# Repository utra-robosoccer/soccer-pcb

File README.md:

TODO's
  - SPI com between mcus
  - validate pinout with firmware
  -

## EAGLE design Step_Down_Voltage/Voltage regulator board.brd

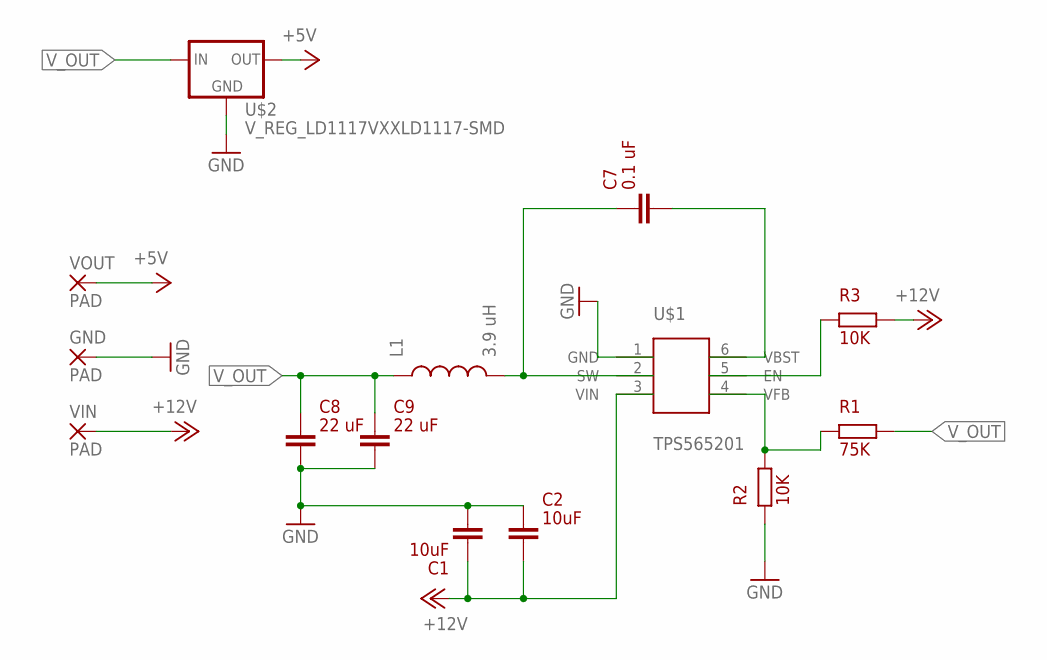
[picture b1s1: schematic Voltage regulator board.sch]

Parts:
C1, C2: 10uF; C1206K
C7: 0.1 uF; C1206K
C8, C9: 22 uF; C1206K
GND: PAD
L1: 3.9 uH; SRN6028
R1: 75K; C0603K
R2, R3: 10K; C0603K
U$1: TPS565201; SOT23-6
U$2: V_REG_LD1117VXXLD1117-SMD; SOT223
VIN: PAD
VOUT: PAD

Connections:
+5V: U$2.2 (OUT), VOUT.1
+12V: C1.1, C2.2, R3.2, U$1.3 (VIN), VIN.1
GND: C1.2, C2.1, C8.2, C9.2, GND.1, R2.1, U$1.1 (GND), U$2.1 (GND)
unnamed: C7.1, L1.P$2 (2), U$1.2 (SW)
unnamed: R1.1, R2.2, U$1.4 (VFB)
unnamed: R3.1, U$1.5 (EN)
unnamed: C7.2, U$1.6 (VBST)
V_OUT: C8.1, C9.1, L1.P$1 (1), R1.2, U$2.3 (IN)

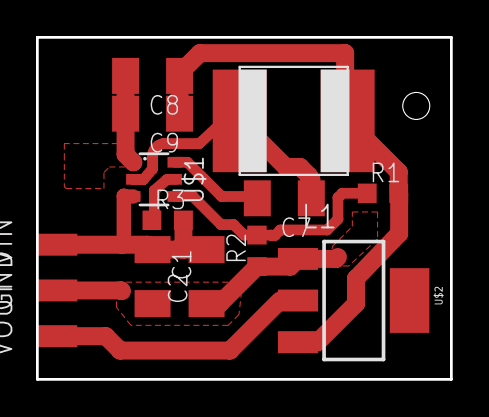
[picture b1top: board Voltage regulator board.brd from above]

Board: 2 copper layers, 23.0 x 19.0 mm, 14 parts (0 on the bottom side), 8 nets.

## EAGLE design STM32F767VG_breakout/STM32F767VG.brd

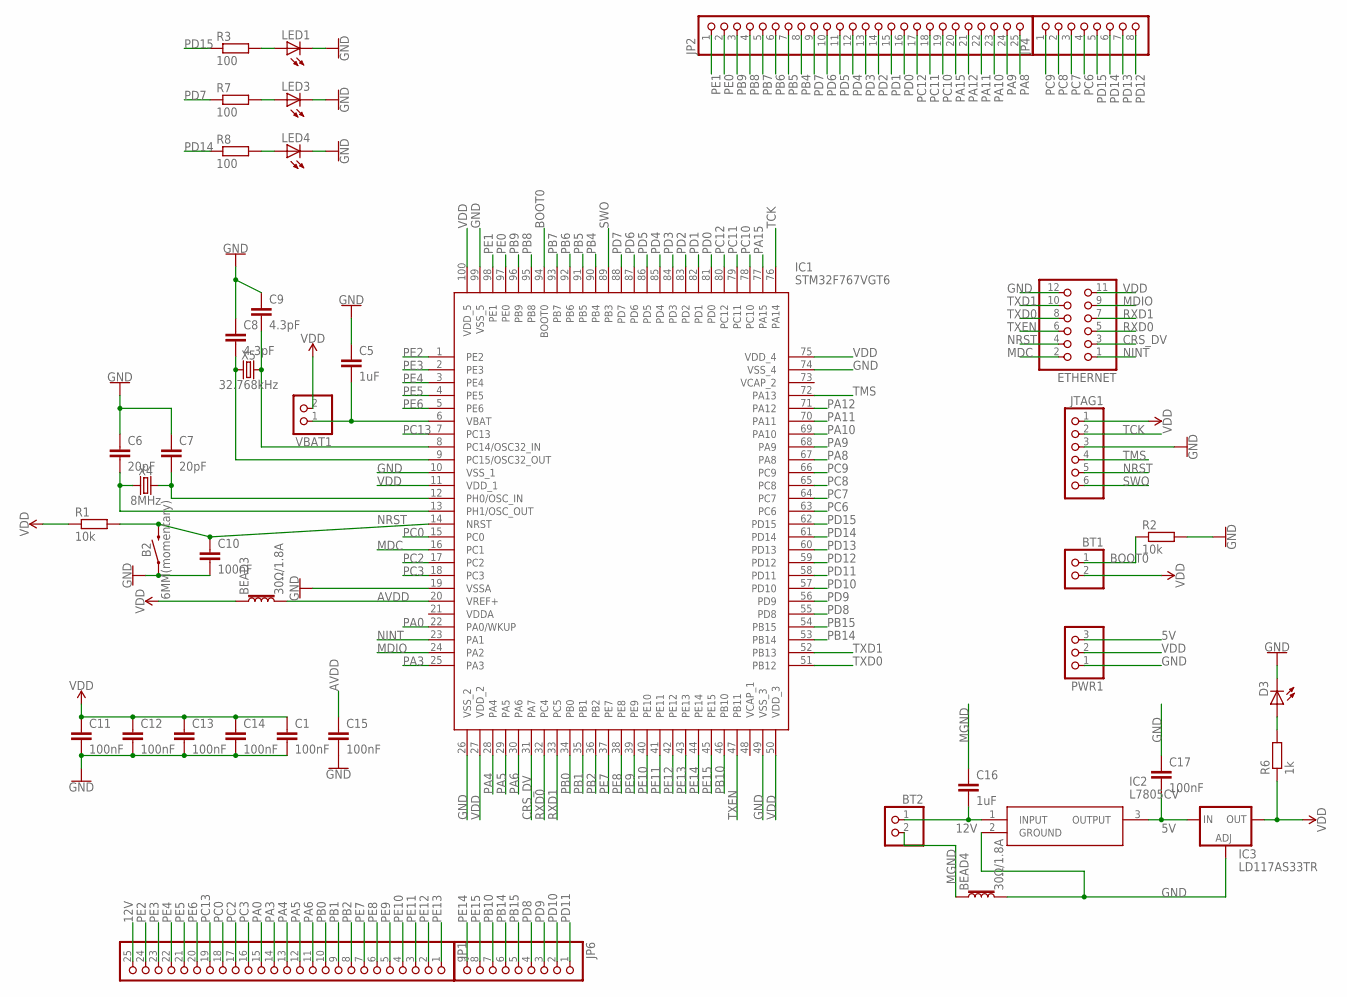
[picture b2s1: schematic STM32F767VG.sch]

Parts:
B2: 6MM(momentary); TACTILE_SWITCH_PTH_6.0MM
BEAD3, BEAD4: 30Ω/1.8A; 0603
BT1, BT2: PINHD-1X2; 1X02
C1, C10, C11, C12, C13, C14, C15, C17: 100nF; C0805
C5, C16: 1uF; C0805
C6, C7: 20pF; C0805
C8, C9: 4.3pF; C0805
D3: LED_E; LED_1206
ETHERNET: PINHD-2X6; 2X06
IC1: STM32F767VGT6; QFP50P1600X1600X160-100N
IC2: L7805CV; TO270P460X1020X2008-3P
IC3: LD117AS33TR; SOT223
JP1, JP2: PINHD-1X25; 1X25
JP4: PINHD-1X8; 1X08
JP6: PINHD-1X9; 1X09
JTAG1: PINHD-1X6; 1X06
LED1, LED3, LED4: LED_E; LED_1206
PWR1: PINHD-1X3; 1X03
R1, R2: 10k; R0805
R3, R7, R8: 100; R0805
R6: 1k; R0805
VBAT1: PINHD-1X2; 1X02
X4: 8MHz; HC49UP
X5: 32.768kHz; CRYSTAL-PTH-2X6-CYL

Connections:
5V: C17.2, IC2.3 (OUTPUT), IC3.3 (IN), PWR1.3
12V: BT2.1, C16.2, IC2.1 (INPUT), JP1.25
AVDD: BEAD3.2, C15.1, IC1.20 (VREF+)
BOOT0: BT1.1, IC1.94 (BOOT0), R2.1
CRS_DV: ETHERNET.3, IC1.31 (PA7)
GND: B2.1, BEAD4.2, C1.2, C5.1, C6.1, C7.1, C8.1, C9.1, C10.2, C11.2, C12.2, C13.2, C14.2, C15.2, C17.1, D3.C, ETHERNET.12, IC1.10 (VSS_1), IC1.19 (VSSA), IC1.26 (VSS_2), IC1.49 (VSS_3), IC1.74 (VSS_4), IC1.99 (VSS_5), IC2.2 (GROUND), IC3.1 (ADJ), JTAG1.3, LED1.C, LED3.C, LED4.C, PWR1.1, R2.2
MDC: ETHERNET.2, IC1.16 (PC1)
MDIO: ETHERNET.9, IC1.24 (PA2)
MGND: BEAD4.1, BT2.2, C16.1
unnamed: C5.2, IC1.6 (VBAT), VBAT1.1
unnamed: C9.2, IC1.8 (PC14/OSC32_IN), X5.2
unnamed: C8.2, IC1.9 (PC15/OSC32_OUT), X5.1
unnamed: LED1.A, R3.2
unnamed: C6.2, IC1.13 (PH1/OSC_OUT), X4.1
unnamed: C7.2, IC1.12 (PH0/OSC_IN), X4.2
unnamed: D3.A, R6.2
unnamed: LED3.A, R7.2
unnamed: LED4.A, R8.2
NINT: ETHERNET.1, IC1.23 (PA1)
NRST: B2.3 (2), C10.1, ETHERNET.4, IC1.14 (NRST), JTAG1.5, R1.2
PA0: IC1.22 (PA0/WKUP), JP1.15
PA3: IC1.25 (PA3), JP1.14
PA4: IC1.28 (PA4), JP1.13
PA5: IC1.29 (PA5), JP1.12
PA6: IC1.30 (PA6), JP1.11
PA8: IC1.67 (PA8), JP2.25
PA9: IC1.68 (PA9), JP2.24
PA10: IC1.69 (PA10), JP2.23
PA11: IC1.70 (PA11), JP2.22
PA12: IC1.71 (PA12), JP2.21
PA15: IC1.77 (PA15), JP2.20
PB0: IC1.34 (PB0), JP1.10
PB1: IC1.35 (PB1), JP1.9
PB2: IC1.36 (PB2), JP1.8
PB4: IC1.90 (PB4), JP2.8
PB5: IC1.91 (PB5), JP2.7
PB6: IC1.92 (PB6), JP2.6
PB7: IC1.93 (PB7), JP2.5
PB8: IC1.95 (PB8), JP2.4
PB9: IC1.96 (PB9), JP2.3
PB10: IC1.46 (PB10), JP6.7
PB14: IC1.53 (PB14), JP6.6
PB15: IC1.54 (PB15), JP6.5
PC0: IC1.15 (PC0), JP1.18
PC2: IC1.17 (PC2), JP1.17
PC3: IC1.18 (PC3), JP1.16
PC6: IC1.63 (PC6), JP4.4
PC7: IC1.64 (PC7), JP4.3
PC8: IC1.65 (PC8), JP4.2
PC9: IC1.66 (PC9), JP4.1
PC10: IC1.78 (PC10), JP2.19
PC11: IC1.79 (PC11), JP2.18
PC12: IC1.80 (PC12), JP2.17
PC13: IC1.7 (PC13), JP1.19
PD0: IC1.81 (PD0), JP2.16
PD1: IC1.82 (PD1), JP2.15
PD2: IC1.83 (PD2), JP2.14
PD3: IC1.84 (PD3), JP2.13
PD4: IC1.85 (PD4), JP2.12
PD5: IC1.86 (PD5), JP2.11
PD6: IC1.87 (PD6), JP2.10
PD7: IC1.88 (PD7), JP2.9, R7.1
PD8: IC1.55 (PD8), JP6.4
PD9: IC1.56 (PD9), JP6.3
PD10: IC1.57 (PD10), JP6.2
PD11: IC1.58 (PD11), JP6.1
PD12: IC1.59 (PD12), JP4.8
PD13: IC1.60 (PD13), JP4.7
PD14: IC1.61 (PD14), JP4.6, R8.1
PD15: IC1.62 (PD15), JP4.5, R3.1
PE0: IC1.97 (PE0), JP2.2
PE1: IC1.98 (PE1), JP2.1
PE2: IC1.1 (PE2), JP1.24
PE3: IC1.2 (PE3), JP1.23
PE4: IC1.3 (PE4), JP1.22
PE5: IC1.4 (PE5), JP1.21
PE6: IC1.5 (PE6), JP1.20
PE7: IC1.37 (PE7), JP1.7
PE8: IC1.38 (PE8), JP1.6
PE9: IC1.39 (PE9), JP1.5
PE10: IC1.40 (PE10), JP1.4
PE11: IC1.41 (PE11), JP1.3
PE12: IC1.42 (PE12), JP1.2
PE13: IC1.43 (PE13), JP1.1
PE14: IC1.44 (PE14), JP6.9
PE15: IC1.45 (PE15), JP6.8
RXD0: ETHERNET.5, IC1.32 (PC4)
RXD1: ETHERNET.7, IC1.33 (PC5)
SWO: IC1.89 (PB3), JTAG1.6
TCK: IC1.76 (PA14), JTAG1.2
TMS: IC1.72 (PA13), JTAG1.4
TXD0: ETHERNET.8, IC1.51 (PB12)
TXD1: ETHERNET.10, IC1.52 (PB13)
TXEN: ETHERNET.6, IC1.47 (PB11)
VCAP_1: IC1.48 (VCAP_1)
VCAP_2: IC1.73 (VCAP_2)
VDD: BEAD3.1, BT1.2, C1.1, C11.1, C12.1, C13.1, C14.1, ETHERNET.11, IC1.11 (VDD_1), IC1.27 (VDD_2), IC1.50 (VDD_3), IC1.75 (VDD_4), IC1.100 (VDD_5), IC3.4 (OUT), JTAG1.1, PWR1.2, R1.1, R6.1, VBAT1.2
VDDA: IC1.21 (VDDA)

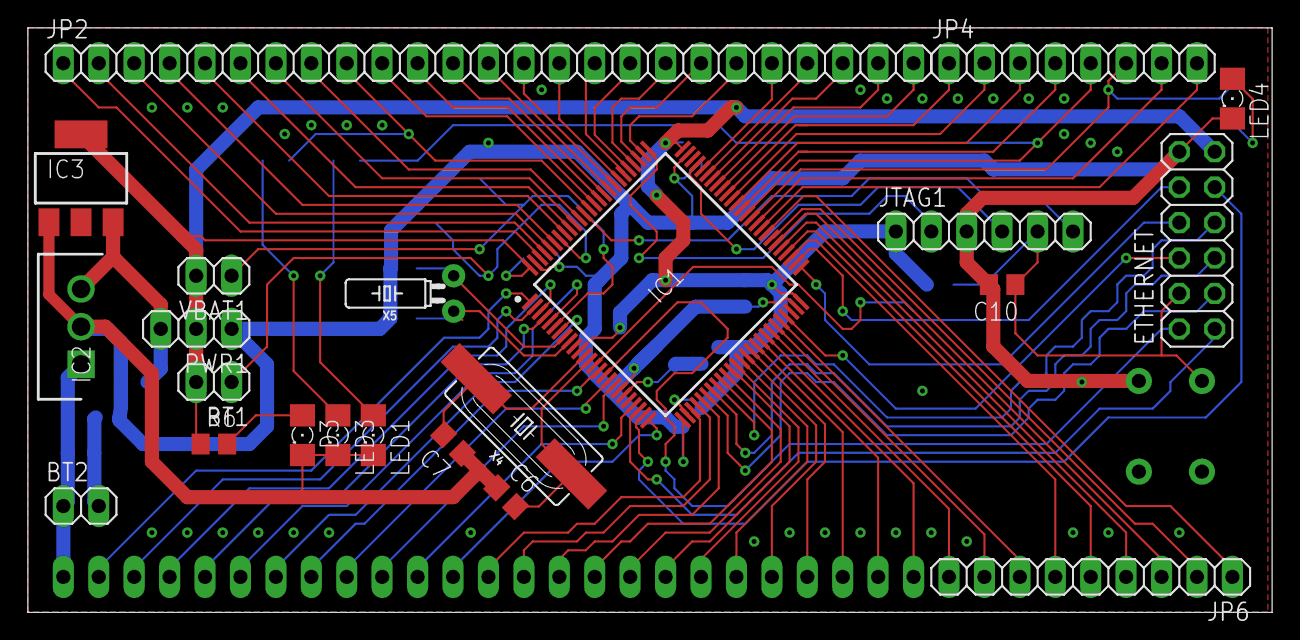
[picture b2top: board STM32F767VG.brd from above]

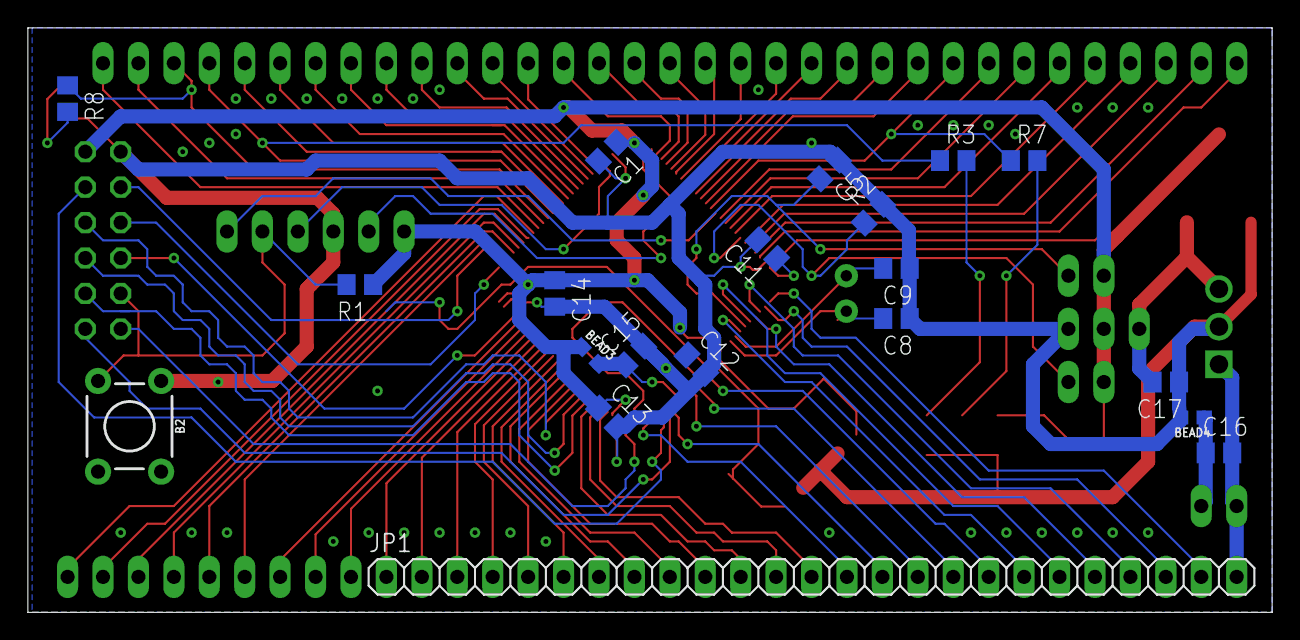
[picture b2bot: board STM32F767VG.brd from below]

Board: 2 copper layers, 89.2 x 41.9 mm, 42 parts (20 on the bottom side), 95 nets.

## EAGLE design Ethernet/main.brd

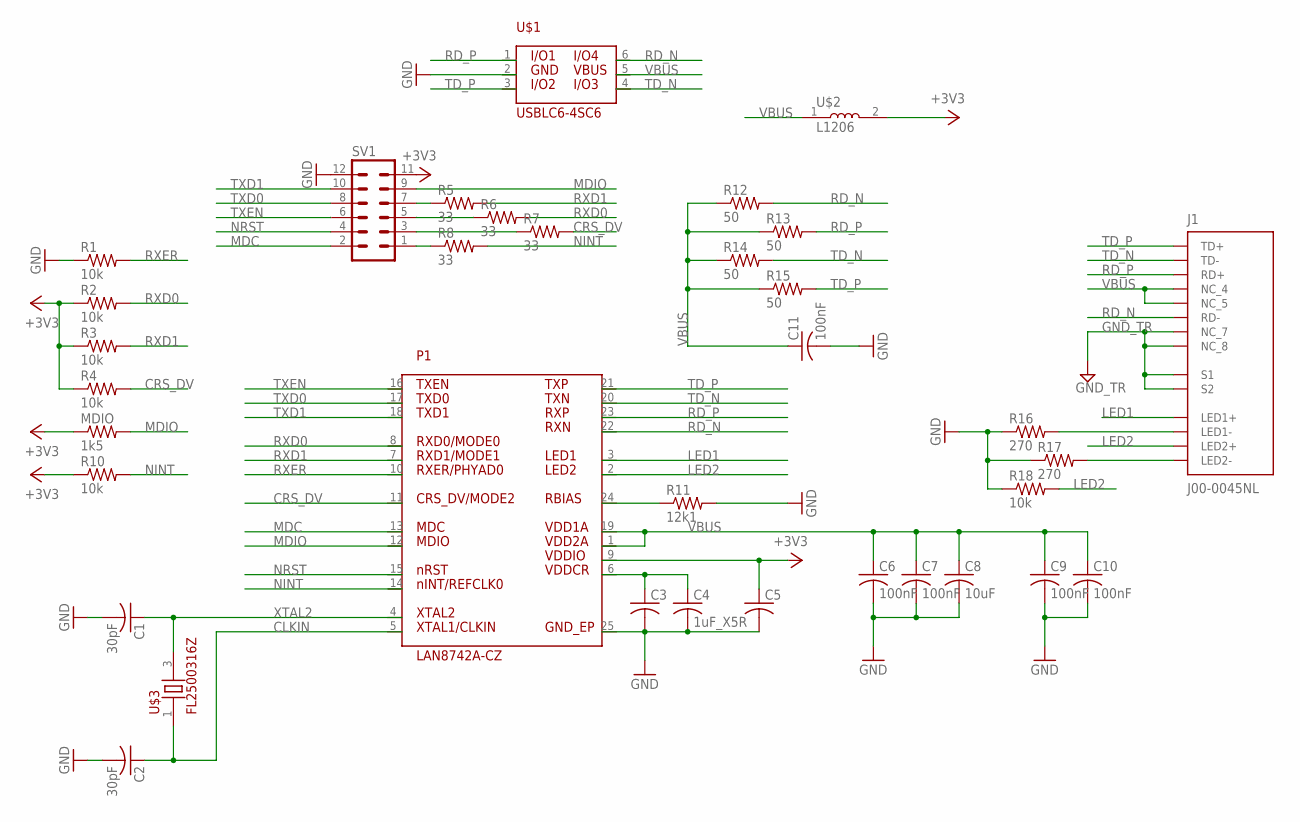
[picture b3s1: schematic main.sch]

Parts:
C1, C2: 30pF; C0603
C3, C5: C-USC0603; C0603
C4: 1uF_X5R; C0603
C6, C7, C9, C10, C11: 100nF; C0603
C8: 10uF; C1206K
J1: J00-0045NL; PULSE_J00-0045NL
MDIO: 1k5; R0603
P1: LAN8742A-CZ
R1, R2, R3, R4, R10, R18: 10k; R0603
R5, R6, R7, R8: 33; R0603
R11: 12k1; R0603
R12, R13, R14, R15: 50; R0603
R16, R17: 270; R0603
SV1: MA06-2
U$1: USBLC6-4SC6; SOT95P280X145-6N
U$2: L1206; RESC3216X125N
U$3: FL2500316Z

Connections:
+3V3: C5.1, MDIO.1, P1.9, R2.1, R3.1, R4.1, R10.1, SV1.11, U$2.2
CLKIN: C2.1, P1.5, U$3.1
CRS_DV: P1.11, R4.2, R7.2
GND: C1.2, C2.2, C3.2, C4.2, C5.2, C6.2, C7.2, C8.2, C9.2, C10.2, C11.2, P1.25, R1.1, R11.2, R16.1, R17.1, R18.1, SV1.12, U$1.2
GND_TR: J1.7 (NC_7), J1.8 (NC_8), J1.S1, J1.S2
LED1: J1.9 (LED1+), P1.3
LED2: J1.12 (LED2+), P1.2, R18.2
MDC: P1.13, SV1.2
MDIO: MDIO.2, P1.12, SV1.9
unnamed: R5.1, SV1.7
unnamed: R6.1, SV1.5
unnamed: P1.24, R11.1
unnamed: R7.1, SV1.3
unnamed: R8.1, SV1.1
unnamed: C3.1, C4.1, P1.6
unnamed: J1.10 (LED1-), R16.2
unnamed: J1.11 (LED2-), R17.2
NINT: P1.14, R8.2, R10.2
NRST: P1.15, SV1.4
RD_N: J1.6 (RD-), P1.22, R12.2, U$1.6
RD_P: J1.3 (RD+), P1.23, R13.2, U$1.1
RXD0: P1.8, R2.2, R6.2
RXD1: P1.7, R3.2, R5.2
RXER: P1.10, R1.2
TD_N: J1.2 (TD-), P1.20, R14.2, U$1.4
TD_P: J1.1 (TD+), P1.21, R15.2, U$1.3
TXD0: P1.17, SV1.8
TXD1: P1.18, SV1.10
TXEN: P1.16, SV1.6
VBUS: C6.1, C7.1, C8.1, C9.1, C10.1, C11.1, J1.4 (NC_4), J1.5 (NC_5), P1.1, P1.19, R12.1, R13.1, R14.1, R15.1, U$1.5, U$2.1
XTAL2: C1.1, P1.4, U$3.3

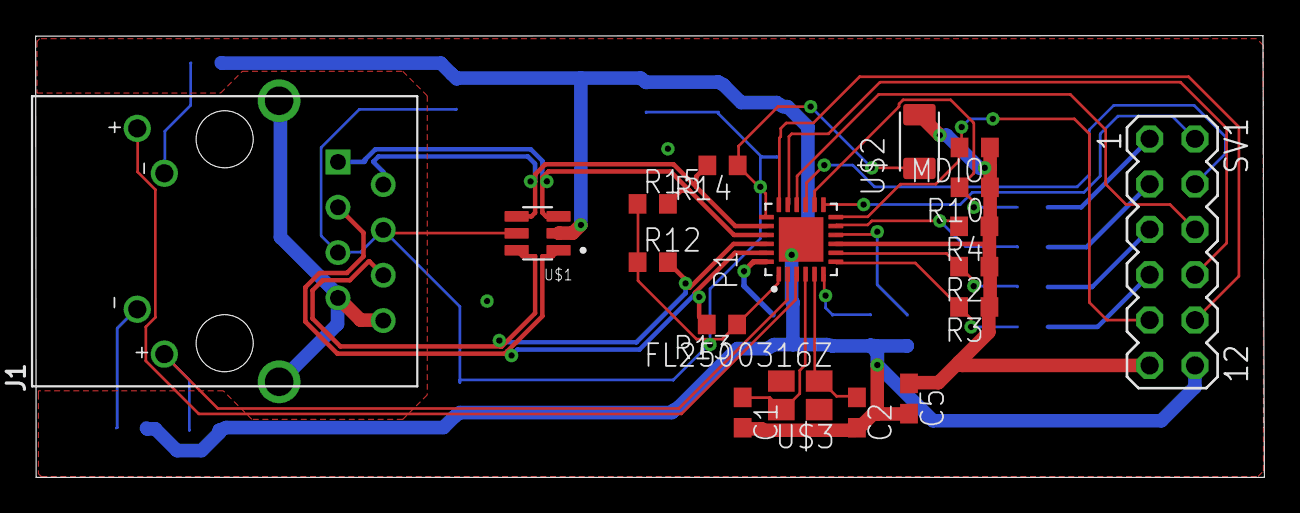
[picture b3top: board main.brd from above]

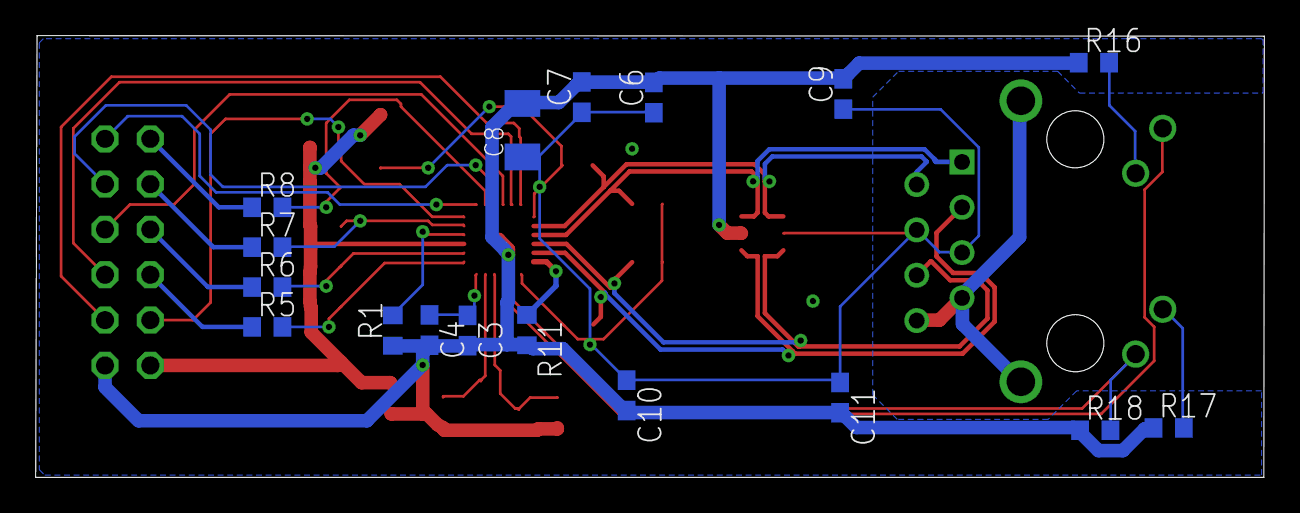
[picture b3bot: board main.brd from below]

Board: 2 copper layers, 68.9 x 24.8 mm, 35 parts (17 on the bottom side), 31 nets.

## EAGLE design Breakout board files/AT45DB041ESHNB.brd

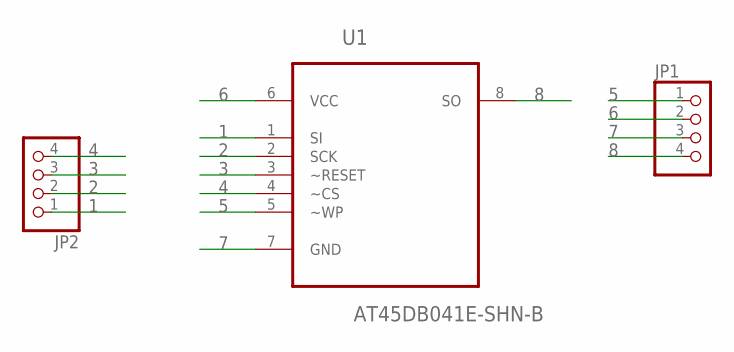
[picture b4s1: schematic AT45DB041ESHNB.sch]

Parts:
JP1, JP2: PINHD-1X4; 1X04
U1: AT45DB041E-SHN-B; SOIC127P798X216-8N

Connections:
1: JP2.1, U1.1 (SI)
2: JP2.2, U1.2 (SCK)
3: JP2.3, U1.3 (~RESET)
4: JP2.4, U1.4 (~CS)
5: JP1.1, U1.5 (~WP)
6: JP1.2, U1.6 (VCC)
7: JP1.3, U1.7 (GND)
8: JP1.4, U1.8 (SO)

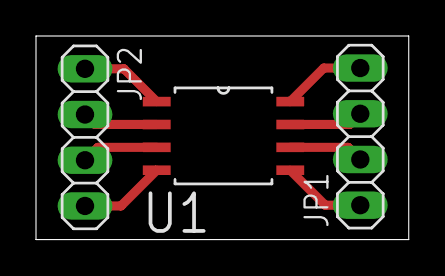
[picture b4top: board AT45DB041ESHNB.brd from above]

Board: 2 copper layers, 20.7 x 11.3 mm, 3 parts (0 on the bottom side), 8 nets.

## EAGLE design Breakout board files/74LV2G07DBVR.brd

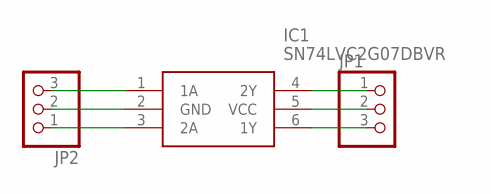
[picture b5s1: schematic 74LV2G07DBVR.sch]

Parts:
IC1: SN74LVC2G07DBVR; SOT95P280X145-6N
JP1, JP2: PINHD-1X3; 1X03

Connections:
unnamed: IC1.2 (GND), JP2.2
unnamed: IC1.1 (1A), JP2.3
unnamed: IC1.3 (2A), JP2.1
unnamed: IC1.6 (1Y), JP1.3
unnamed: IC1.4 (2Y), JP1.1
unnamed: IC1.5 (VCC), JP1.2

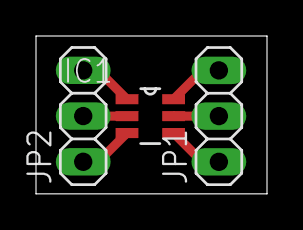
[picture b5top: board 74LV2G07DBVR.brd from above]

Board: 2 copper layers, 12.8 x 8.8 mm, 3 parts (0 on the bottom side), 6 nets.

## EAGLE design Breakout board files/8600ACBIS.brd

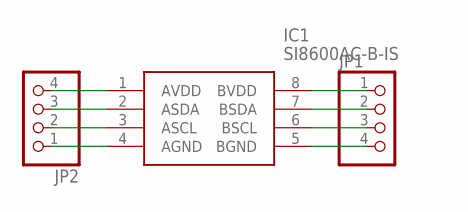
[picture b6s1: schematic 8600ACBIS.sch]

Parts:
IC1: SI8600AC-B-IS; SOIC127P600X175-8N
JP1, JP2: PINHD-1X4; 1X04

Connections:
unnamed: IC1.1 (AVDD), JP2.4
unnamed: IC1.2 (ASDA), JP2.3
unnamed: IC1.3 (ASCL), JP2.2
unnamed: IC1.4 (AGND), JP2.1
unnamed: IC1.8 (BVDD), JP1.1
unnamed: IC1.7 (BSDA), JP1.2
unnamed: IC1.6 (BSCL), JP1.3
unnamed: IC1.5 (BGND), JP1.4

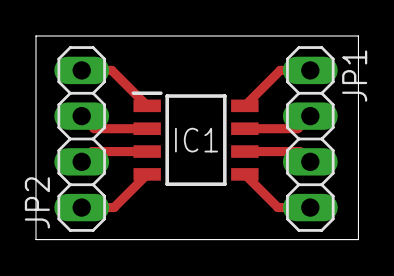
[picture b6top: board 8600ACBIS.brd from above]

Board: 2 copper layers, 17.9 x 11.3 mm, 3 parts (0 on the bottom side), 8 nets.

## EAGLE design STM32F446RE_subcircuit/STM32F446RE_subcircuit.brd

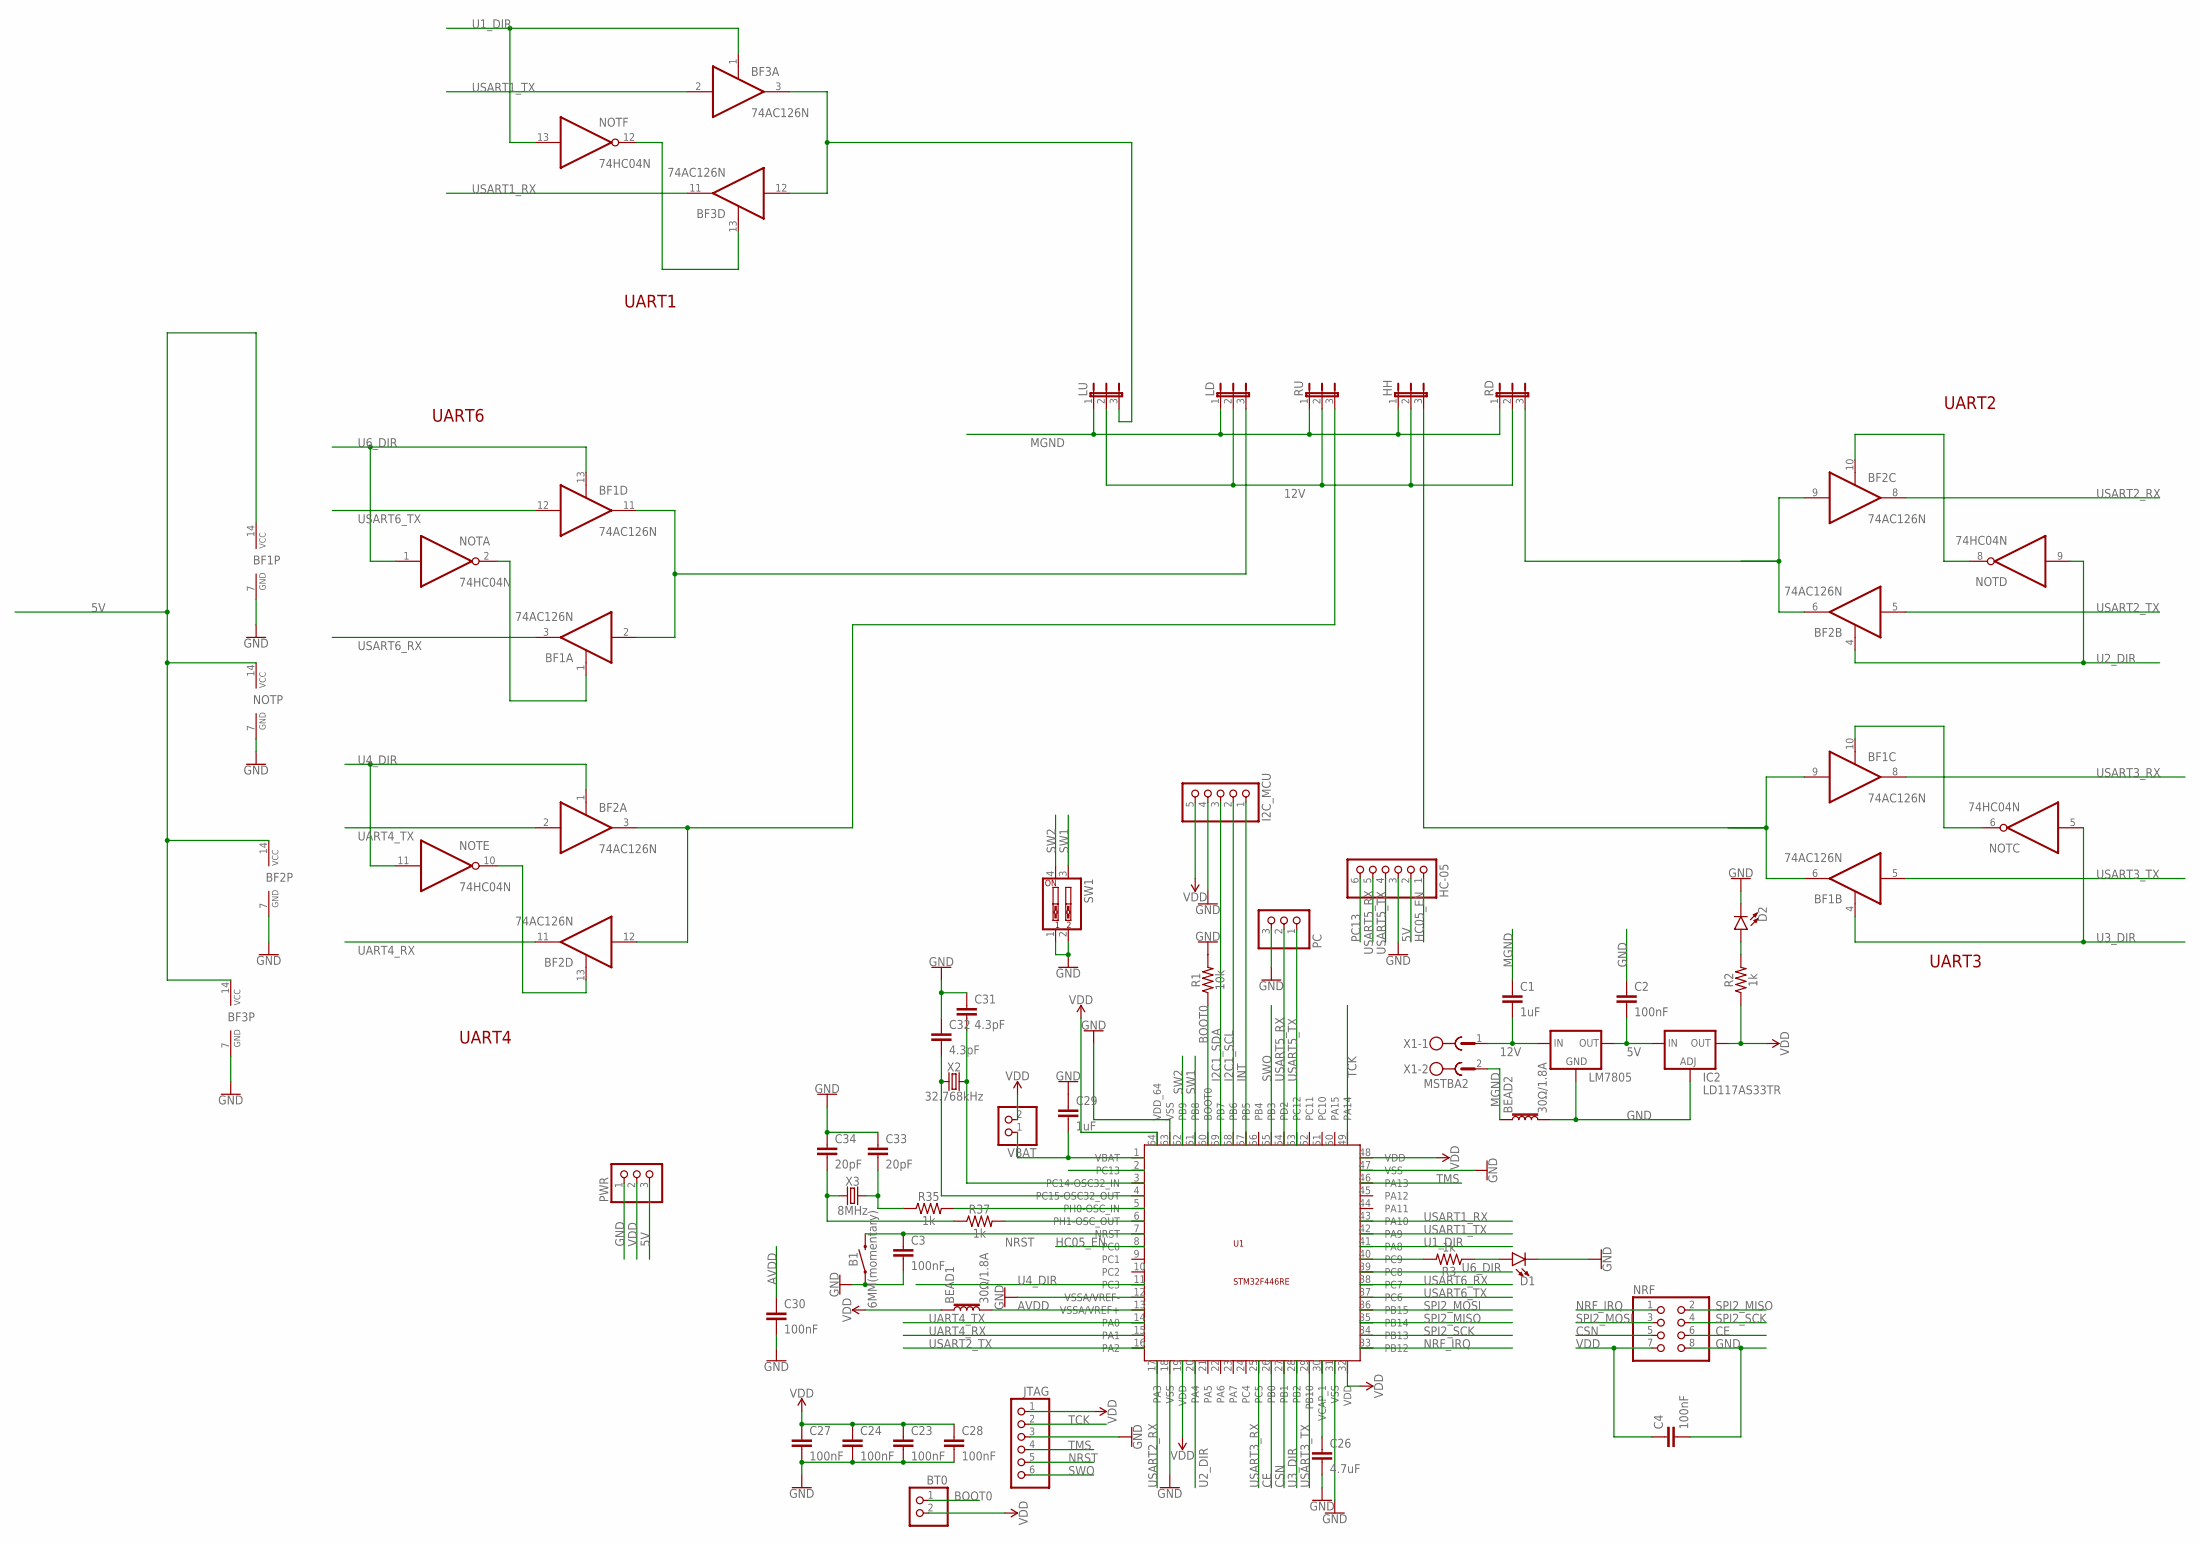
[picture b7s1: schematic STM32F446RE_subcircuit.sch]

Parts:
B1: 6MM(momentary); TACTILE_SWITCH_PTH_6.0MM
BEAD1, BEAD2: 30Ω/1.8A; 0603
BF1, BF2, BF3: 74AC126N; DIL14
BT0: PINHD-1X2; 1X02
C1, C29: 1uF; C050-030-075
C2, C3, C4, C23, C24, C27, C28, C30: 100nF; C025-030X050
C26: 4.7uF; C050-030-075
C31, C32: 4.3pF; C025-030X050
C33, C34: 20pF; C025-030X050
D1, D2: LED5MM; LED_5MM
HC-05: PINHD-1X6; 1X06
HH: JP2E; JP2
I2C_MCU: PINHD-1X5; 1X05
IC2: LD117AS33TR; SOT223
JTAG: PINHD-1X6; 1X06
LD: JP2E; JP2
LM7805: V_REG_78XX-TO-220; TO-220-ALT
LU: JP2E; JP2
NOT: 74HC04N; DIL14
NRF: PINHD-2X4; 2X04
PC: PINHD-1X3; 1X03
PWR: PINHD-1X3; 1X03
R1: 10k; AXIAL-0.3
R2, R3, R35, R37: 1k; AXIAL-0.3
RD: JP2E; JP2
RU: JP2E; JP2
SW1: SW_DIP-2; EDG-02
U1: STM32F446RE; QFP50P1200X1200X160-64N
VBAT: PINHD-1X2; 1X02
X1: MSTBA2
X2: 32.768kHz; CRYSTAL-PTH-2X6-CYL
X3: 8MHz; HC49UP

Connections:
5V: BF1.14 (VCC), BF2.14 (VCC), BF3.14 (VCC), C2.2, HC-05.2, IC2.3 (IN), LM7805.OUT, NOT.14 (VCC), PWR.3
12V: C1.2, HH.2, LD.2, LM7805.IN, LU.2, RD.2, RU.2, X1.1
AVDD: BEAD1.2, C30.1, U1.13 (VSSA/VREF+)
BOOT0: BT0.1, R1.P$1 (1), U1.60 (BOOT0)
CE: NRF.6, U1.26 (PB0)
CSN: NRF.5, U1.27 (PB1)
GND: B1.1, BEAD2.2, BF1.7 (GND), BF2.7 (GND), BF3.7 (GND), C2.1, C3.2, C4.2, C23.2, C24.2, C26.2, C27.2, C28.2, C29.1, C30.2, C31.1, C32.1, C33.1, C34.1, D1.K (C), D2.K (C), HC-05.3, I2C_MCU.4, IC2.1 (ADJ), JTAG.3, LM7805.GND, NOT.7 (GND), NRF.8, PC.3, PWR.1, R1.P$2 (2), SW1.1, SW1.2, U1.12 (VSSA/VREF-), U1.18 (VSS), U1.31 (VSS), U1.47 (VSS), U1.63 (VSS)
HC05_EN: HC-05.1, U1.8 (PC0)
I2C1_SCL: I2C_MCU.2, U1.58 (PB6)
I2C1_SDA: I2C_MCU.3, U1.59 (PB7)
INT: I2C_MCU.1, U1.57 (PB5)
MGND: BEAD2.1, C1.1, HH.1, LD.1, LU.1, RD.1, RU.1, X1.2
unnamed: R35.P$2 (2), U1.5 (PH0-OSC_IN)
unnamed: R37.P$2 (2), U1.6 (PH1-OSC_OUT)
unnamed: BF1.1 (OE), NOT.2 (O)
unnamed: C34.2, R37.P$1 (1), X3.1
unnamed: C33.2, R35.P$1 (1), X3.2
unnamed: BF1.10 (OE), NOT.6 (O)
unnamed: D2.A, R2.P$2 (2)
unnamed: C31.2, U1.3 (PC14-OSC32_IN), X2.2
unnamed: C32.2, U1.4 (PC15-OSC32_OUT), X2.1
unnamed: R3.P$2 (2), U1.40 (PC9)
unnamed: BF2.13 (OE), NOT.10 (O)
unnamed: D1.A, R3.P$1 (1)
unnamed: BF2.10 (OE), NOT.8 (O)
unnamed: BF3.13 (OE), NOT.12 (O)
unnamed: BF3.3 (O), BF3.12 (I), LU.3
NRF_IRQ: NRF.1, U1.33 (PB12)
NRST: B1.3 (2), C3.1, JTAG.5, U1.7 (NRST)
OUT1: BF1.2 (I), BF1.11 (O), LD.3
OUT2: BF2.3 (O), BF2.12 (I), RU.3
OUT3: BF1.6 (O), BF1.9 (I), HH.3
OUT4: BF2.6 (O), BF2.9 (I), RD.3
PC13: HC-05.6, U1.2 (PC13)
SPI2_MISO: NRF.2, U1.35 (PB14)
SPI2_MOSI: NRF.3, U1.36 (PB15)
SPI2_SCK: NRF.4, U1.34 (PB13)
SW1: SW1.3, U1.61 (PB8)
SW2: SW1.4, U1.62 (PB9)
SWO: JTAG.6, U1.55 (PB3)
TCK: JTAG.2, U1.49 (PA14)
TMS: JTAG.4, U1.46 (PA13)
U1_DIR: BF3.1 (OE), NOT.13 (I), U1.41 (PA8)
U2_DIR: BF2.4 (OE), NOT.9 (I), U1.20 (PA4)
U3_DIR: BF1.4 (OE), NOT.5 (I), U1.28 (PB2)
U4_DIR: BF2.1 (OE), NOT.11 (I), U1.11 (PC3)
U6_DIR: BF1.13 (OE), NOT.1 (I), U1.39 (PC8)
UART4_RX: BF2.11 (O), U1.15 (PA1)
UART4_TX: BF2.2 (I), U1.14 (PA0)
USART1_RX: BF3.11 (O), U1.43 (PA10)
USART1_TX: BF3.2 (I), U1.42 (PA9)
USART2_RX: BF2.8 (O), U1.17 (PA3)
USART2_TX: BF2.5 (I), U1.16 (PA2)
USART3_RX: BF1.8 (O), U1.25 (PC5)
USART3_TX: BF1.5 (I), U1.29 (PB10)
USART5_RX: HC-05.5, PC.2, U1.54 (PD2)
USART5_TX: HC-05.4, PC.1, U1.53 (PC12)
USART6_RX: BF1.3 (O), U1.38 (PC7)
USART6_TX: BF1.12 (I), U1.37 (PC6)
VBAT: C29.2, U1.1 (VBAT), VBAT.1
VCAP_1: C26.1, U1.30 (VCAP_1)
VDD: BEAD1.1, BT0.2, C4.1, C23.1, C24.1, C27.1, C28.1, I2C_MCU.5, IC2.4 (OUT), JTAG.1, NRF.7, PWR.2, R2.P$1 (1), U1.19 (VDD), U1.32 (VDD), U1.48 (VDD), U1.64 (VDD_64), VBAT.2

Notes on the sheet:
UART2
UART4
UART6
UART3
UART1

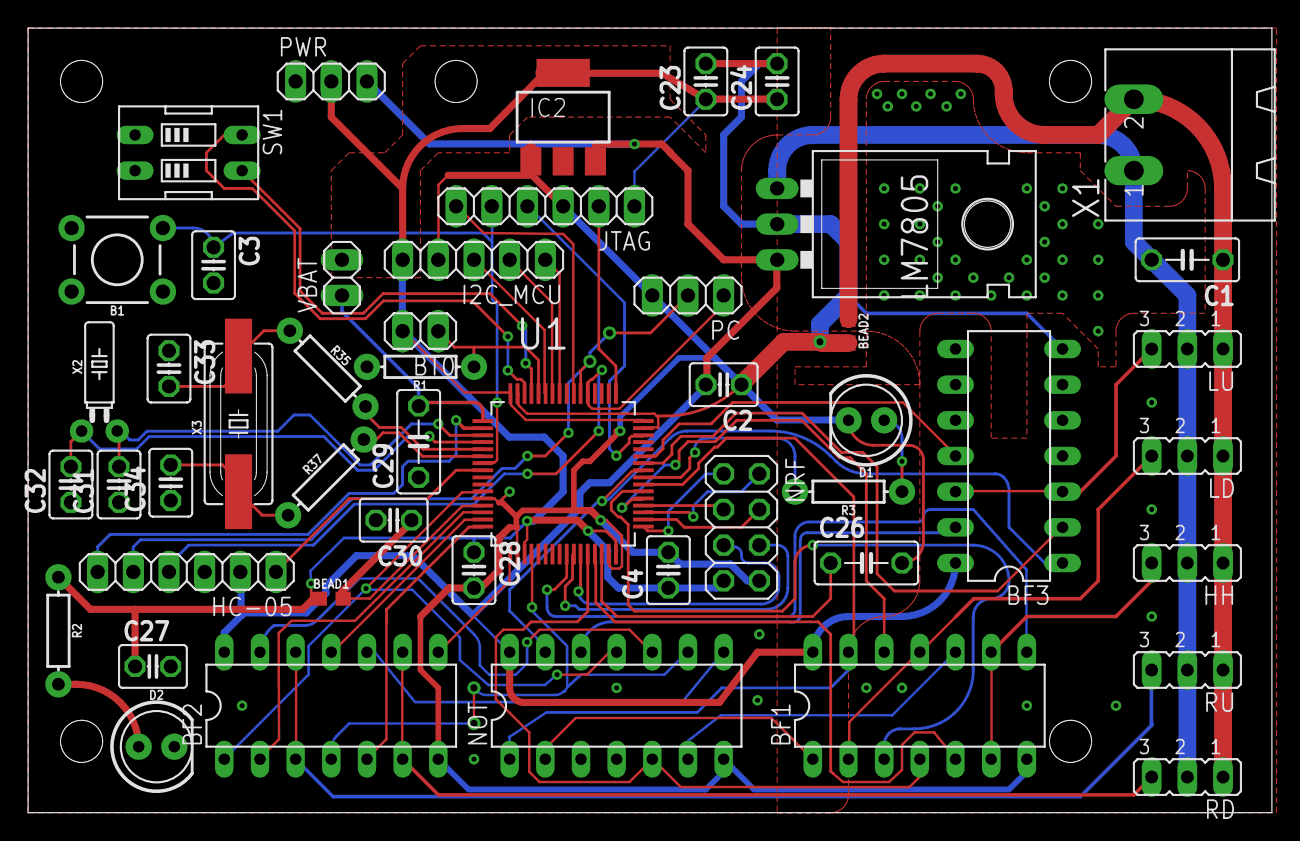
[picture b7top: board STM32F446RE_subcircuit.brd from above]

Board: 2 copper layers, 88.6 x 55.9 mm, 49 parts (0 on the bottom side), 62 nets.

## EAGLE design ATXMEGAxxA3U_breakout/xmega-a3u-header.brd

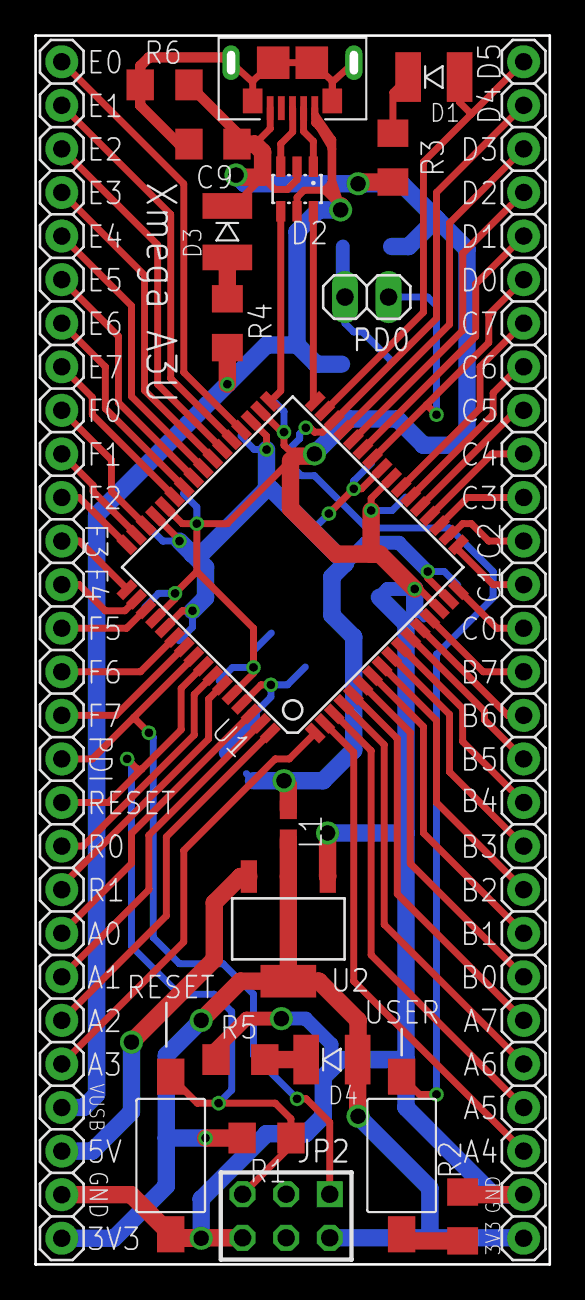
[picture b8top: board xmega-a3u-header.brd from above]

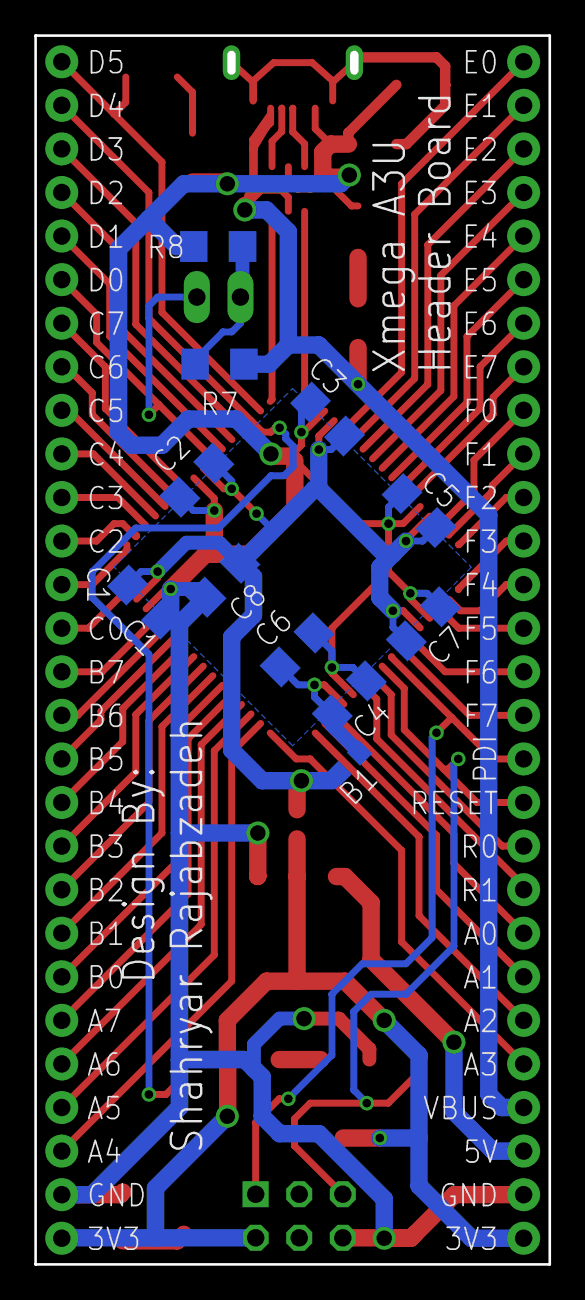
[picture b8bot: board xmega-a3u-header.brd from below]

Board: 2 copper layers, 29.6 x 71.3 mm, 32 parts (11 on the bottom side), 66 nets.

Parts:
B1: FERRITE_BEADB0603; B0603
C1, C2, C3, C5, C7: 100nF; C1206
C4: 100n; C1206
C6, C8: 10u; C1206
C9: 4.7n; C1206
D1, D3, D4: LED; 1210K
D2: ESD_USB; SOT23-6
JP1, JP3: PINHD-1X28SC; 1X28C
JP2: AVR-PDIVERT; AVR-ISP-6
JP4: USB_MICRO_B; USB3076-30-A
L1: 10u; L0603
PD0: 1X02
R1, R4: 10k; R1206
R2, R3, R5, R7: 1k; R1206
R6: 1M; R1206
R8: 1.5k; R1206
RESET: TACTILE-BUTTONSMD-2PIN; FSMSM
U1: XMEGA-A3(U)TQFP; TQFP64
U2: SOT223TAB
USER: TACTILE-BUTTONSMD-2PIN; FSMSM

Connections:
1: C9.2, JP4.BIG_PAD_LEFT, JP4.BIG_PAD_RIGHT, JP4.MECH_RIGHT, JP4.PAD_LEFT, JP4.PAD_RIGHT, JP4.SHIELD_LEFT, R6.1
+3V3: D4.POS, JP1.1, JP2.2, JP3.1, L1.2, R1.2, U2.2, U2.4
+5V: JP3.3, U2.3
D+: D2.3, JP4.D+
D-: D2.1, JP4.D-
DIGITAL_VCC: B1.2, C1.1, C2.1, C3.1, C5.1, C7.1, C8.1, L1.1, U1.15, U1.25, U1.35, U1.45, U1.53
GND: C1.2, C2.2, C3.2, C4.2, C5.2, C6.2, C7.2, C8.2, C9.1, D2.2, D3.NEG, JP1.2, JP2.6, JP3.2, JP4.GND, R2.1, R3.1, R5.1, R6.2, R8.1, RESET.1, U1.14, U1.24, U1.34, U1.44, U1.52, U1.60, U2.1
unnamed: D3.POS, R4.1
unnamed: B1.1, C4.1, C6.1, U1.61
unnamed: R2.2, USER.2
unnamed: D4.NEG, R5.2
unnamed: D1.NEG, R3.2
unnamed: PD0.2, R7.1, R8.2
PA0: JP3.8, U1.62
PA1: JP3.7, U1.63
PA2: JP3.6, U1.64
PA3: JP3.5, U1.1
PA4: JP1.3, U1.2
PA5: JP1.4, U1.3
PA6: JP1.5, U1.4
PA7: JP1.6, U1.5
PB0: JP1.7, U1.6
PB1: JP1.8, U1.7
PB2: JP1.9, U1.8
PB3: JP1.10, U1.9
PB4: JP1.11, U1.10
PB5: JP1.12, U1.11
PB6: JP1.13, U1.12
PB7: JP1.14, U1.13
PC0: JP1.15, U1.16
PC1: JP1.16, U1.17
PC2: JP1.17, U1.18
PC3: JP1.18, U1.19
PC4: JP1.19, U1.20
PC5: JP1.20, U1.21
PC6: JP1.21, U1.22
PC7: JP1.22, U1.23
PD0: JP1.23, PD0.1, U1.26
PD1: JP1.24, U1.27
PD2: JP1.25, U1.28
PD3: JP1.26, U1.29
PD4: JP1.27, U1.30, USER.1
PD5: D1.POS, JP1.28, U1.31
PD6: D2.6, U1.32
PD7: D2.4, U1.33
PDI-CLK: JP2.5, JP3.11, R1.1, RESET.2, U1.57
PDI-DATA: JP2.1, JP3.12, U1.56
PE0: JP3.28, U1.36
PE1: JP3.27, U1.37
PE2: JP3.26, U1.38
PE3: JP3.25, U1.39
PE4: JP3.24, U1.40
PE5: JP3.23, U1.41
PE6: JP3.22, U1.42
PE7: JP3.21, U1.43
PF0: JP3.20, U1.46
PF1: JP3.19, U1.47
PF2: JP3.18, U1.48
PF3: JP3.17, U1.49
PF4: JP3.16, U1.50
PF5: JP3.15, U1.51
PF6: JP3.14, U1.54
PF7: JP3.13, U1.55
PR0: JP3.10, U1.58
PR1: JP3.9, U1.59
VBUS: D2.5, JP3.4, JP4.VBUS, R4.2, R7.2

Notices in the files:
parts and their libraries:
SparkFun-Switches: Licensing: Creative Commons ShareAlike 4.0 International - https://creativecommons.org/licenses/by-sa/4.0
